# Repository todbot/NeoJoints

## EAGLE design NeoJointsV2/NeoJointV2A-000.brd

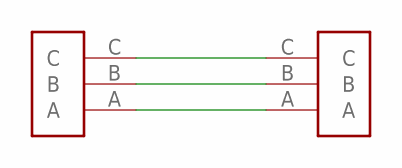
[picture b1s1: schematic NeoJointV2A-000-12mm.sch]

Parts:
U$1, U$2: LED_STRIP_3P; LEDSTRIP-3P

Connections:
A: U$1.A, U$2.A; also elsewhere on the board
B: U$1.B, U$2.B; also elsewhere on the board
C: U$1.C, U$2.C; also elsewhere on the board

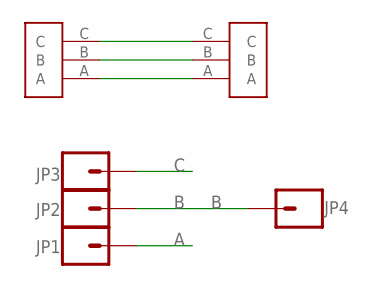
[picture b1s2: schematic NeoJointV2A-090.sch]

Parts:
JP1, JP2, JP3, JP4: M01PTH; 1X01
U$1, U$2: LED_STRIP_3P; LEDSTRIP-3P

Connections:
A: JP1.1, U$1.A, U$2.A
B: JP2.1, JP4.1, U$1.B, U$2.B
C: JP3.1, U$1.C, U$2.C

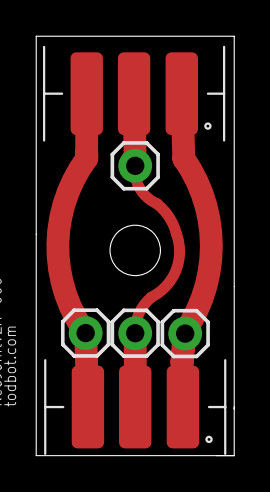
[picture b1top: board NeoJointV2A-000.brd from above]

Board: 2 copper layers, 11.0 x 23.3 mm, 6 parts (0 on the bottom side), 3 nets.

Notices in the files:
parts and their libraries:
SparkFun-Connectors: Licensing: Creative Commons ShareAlike 4.0 International - https://creativecommons.org/licenses/by-sa/4.0
